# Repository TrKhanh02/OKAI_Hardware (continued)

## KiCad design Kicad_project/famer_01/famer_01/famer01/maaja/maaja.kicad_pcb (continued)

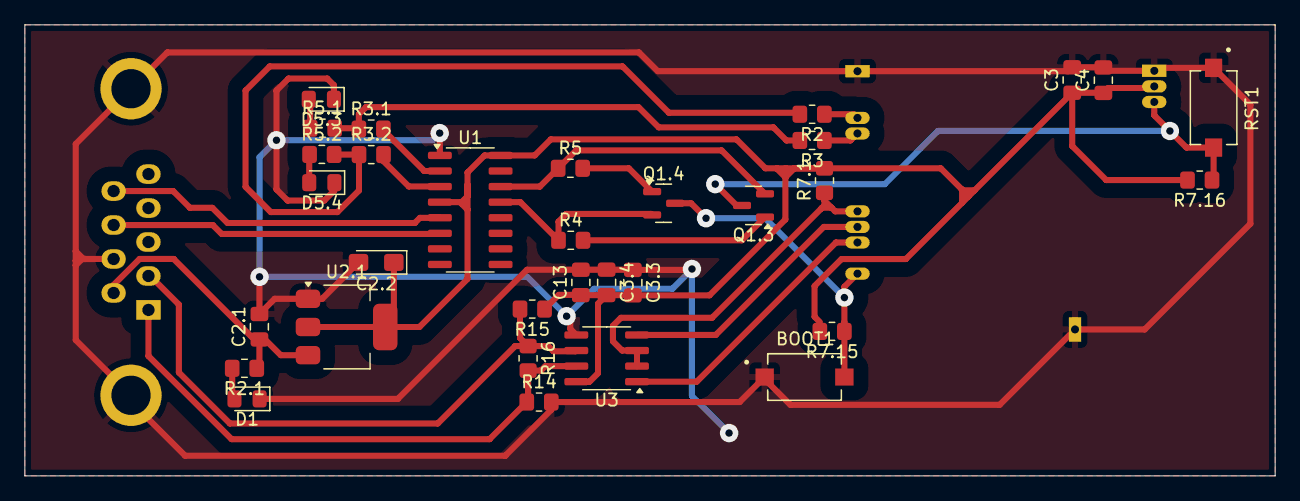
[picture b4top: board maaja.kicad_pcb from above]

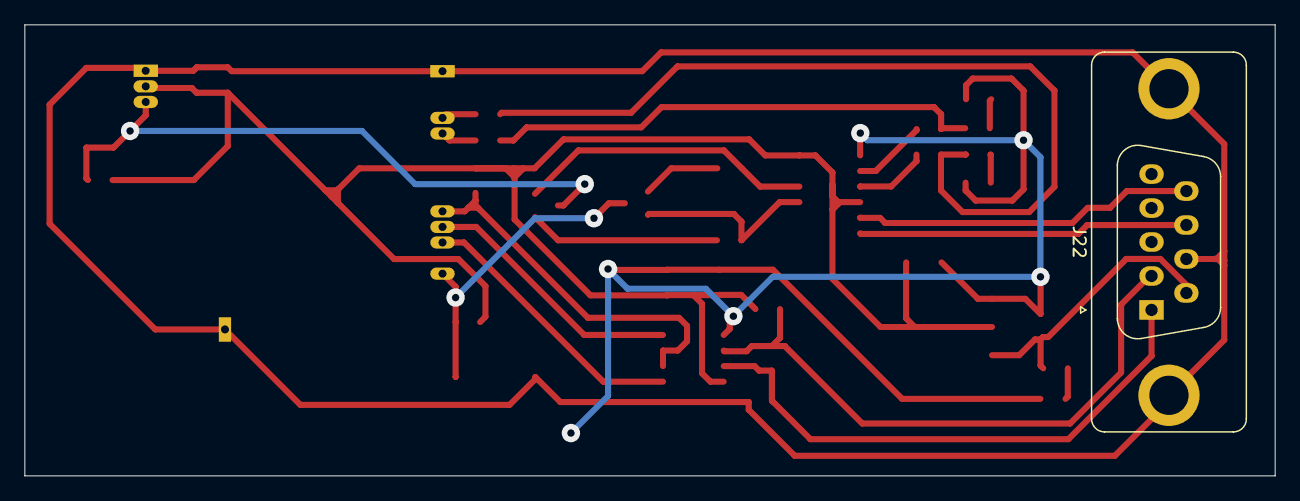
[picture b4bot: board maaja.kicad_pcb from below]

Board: 2 copper layers, 102.0 x 36.8 mm, 34 parts (2 on the bottom side), 25 nets.

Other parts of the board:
C3: 10uF; C_0805_2012Metric_Pad1.18x1.45mm_HandSolder
C4: 0.1uF; C_0805_2012Metric_Pad1.18x1.45mm_HandSolder
J2: ESP32; J header esp32
R7.1: 10k; R_0805_2012Metric_Pad1.20x1.40mm_HandSolder

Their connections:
/3.3V: C3.1, C4.1, J2.2, R7.1.2; also elsewhere on the board
/EN: J2.3; also elsewhere on the board
/IO0: J2.25; also elsewhere on the board
/IO5: J2.29, R7.1.1; also elsewhere on the board
/IO16: J2.27; also elsewhere on the board
/IO17: J2.28; also elsewhere on the board
/MCU_RXD0: J2.34; also elsewhere on the board
/MCU_TXD0: J2.35; also elsewhere on the board
GND: C3.2, C4.2, J2.1, J2.15, J2.38; also elsewhere on the board

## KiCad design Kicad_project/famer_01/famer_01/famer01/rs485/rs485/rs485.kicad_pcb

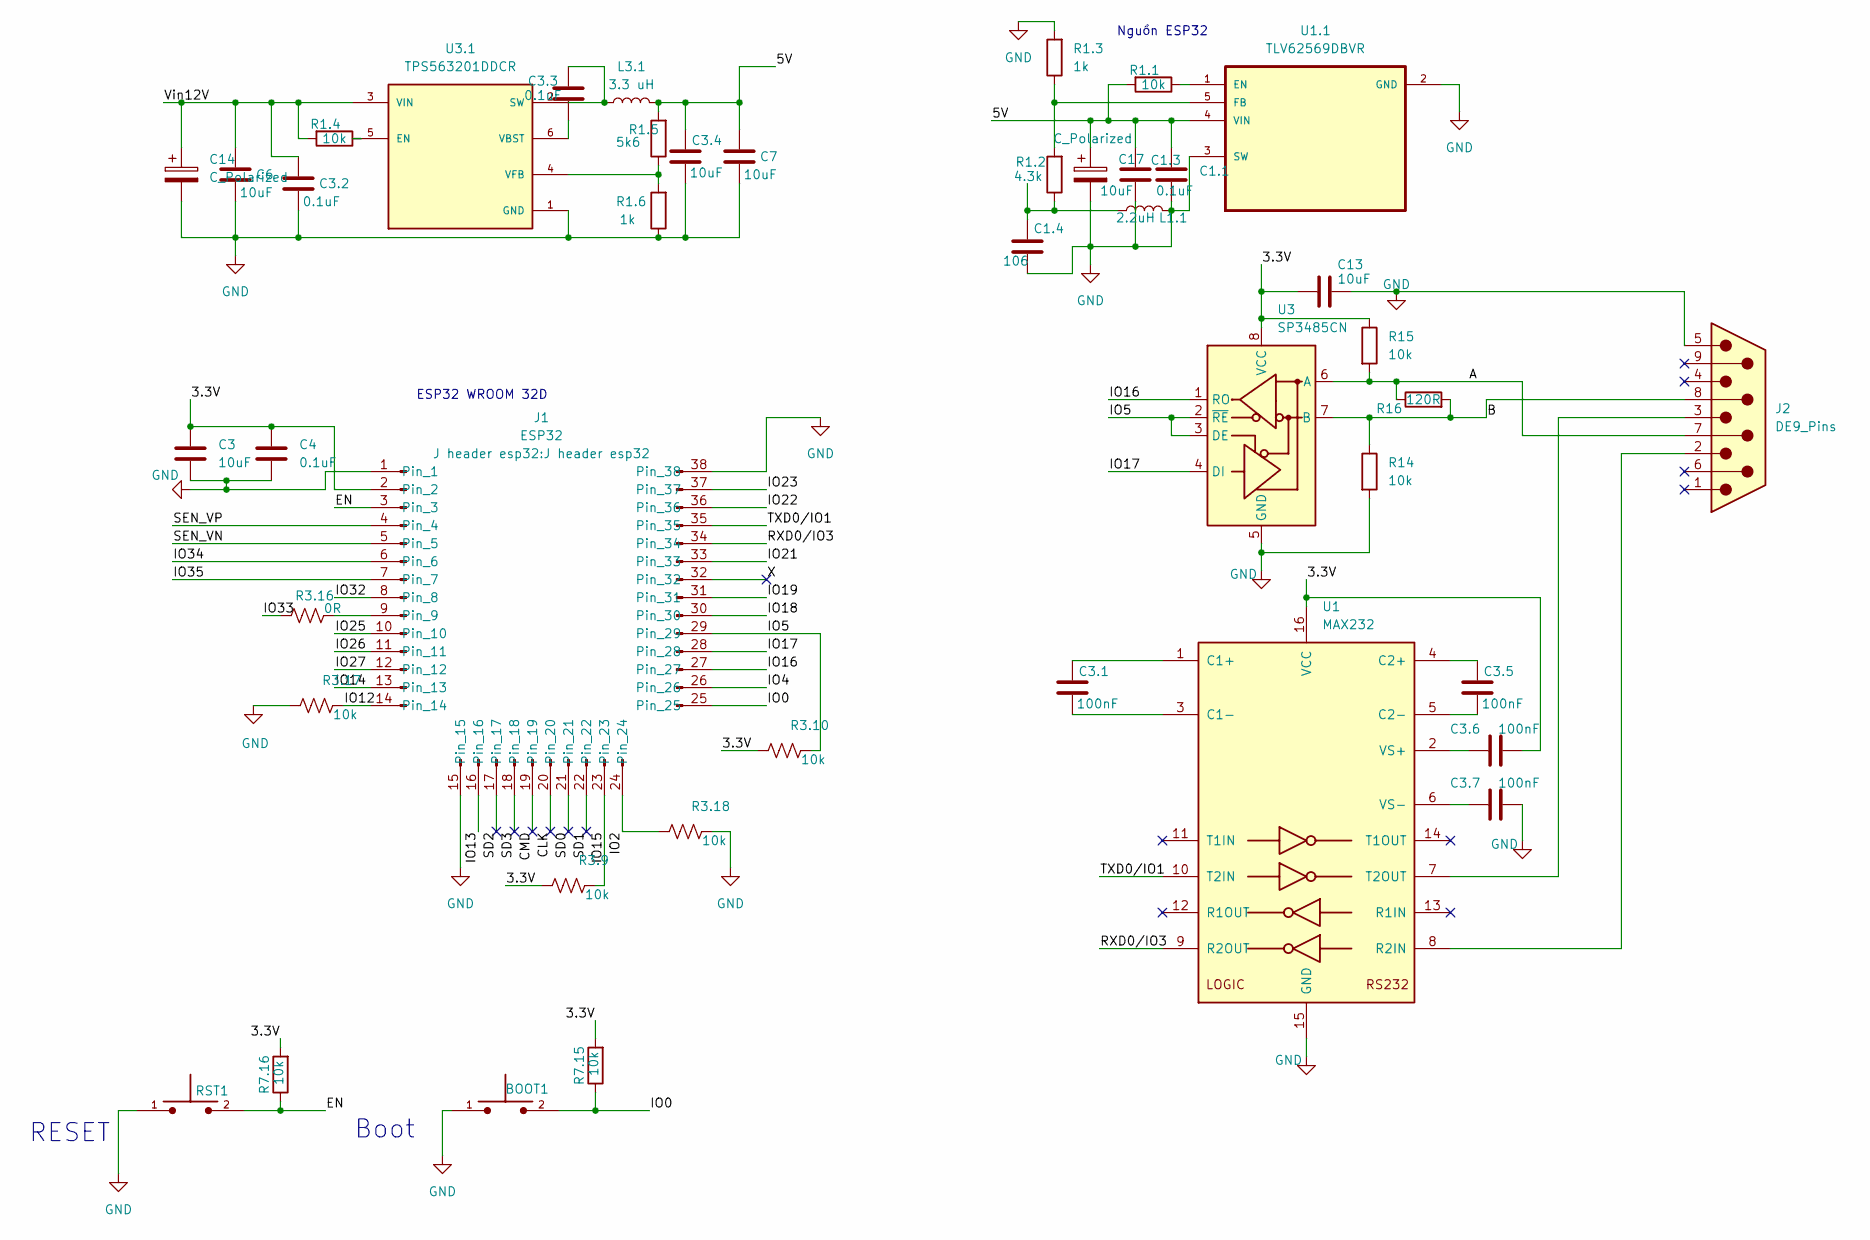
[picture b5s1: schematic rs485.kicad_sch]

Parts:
BOOT1: TS10-63-26-BE-250-SMT-TR; SW_TS10-63-26-BE-250-SMT-TR; PARTREV 1.0
C1.1, C3.2, C3.3, C4: 0.1uF; C_0805_2012Metric_Pad1.18x1.45mm_HandSolder
C1.3, C3, C3.4, C6, C7, C13: 10uF; C_0805_2012Metric_Pad1.18x1.45mm_HandSolder
C1.4: 106; C_0805_2012Metric_Pad1.18x1.45mm_HandSolder
C3.1, C3.5, C3.6, C3.7: 100nF; C_0805_2012Metric_Pad1.18x1.45mm_HandSolder
C14, C17: C_Polarized; CP_Elec_6.3x7.7
J1: ESP32; J header esp32
J2: DE9_Pins; DSUB-9_Pins_Vertical_P2.77x2.84mm
L1.1: 2.2uH; IND_SLF7032T-331MR22-2PF
L3.1: 3.3 uH; IND_SLF7032T-331MR22-2PF
R1.1, R1.4, R3.9, R3.10, R3.17, R3.18, R7.15, R7.16, R14, R15: 10k; R_0805_2012Metric_Pad1.20x1.40mm_HandSolder
R1.2: 4.3k; R_0805_2012Metric_Pad1.20x1.40mm_HandSolder
R1.3, R1.6: 1k; R_0805_2012Metric_Pad1.20x1.40mm_HandSolder
R1.5: 5k6; R_0805_2012Metric_Pad1.20x1.40mm_HandSolder
R3.16: 0R; R_0805_2012Metric_Pad1.20x1.40mm_HandSolder
R16: 120R; R_0805_2012Metric_Pad1.20x1.40mm_HandSolder
RST1: TS10-63-26-BE-250-SMT-TR; SW_TS10-63-26-BE-250-SMT-TR; PARTREV 1.0
U1: MAX232; DIP-16_W7.62mm_SMDSocket_SmallPads
U1.1: TLV62569DBVR; SOT95P280X145-5N
U3: SP3485CN; SOIC-8_3.9x4.9mm_P1.27mm
U3.1: TPS563201DDCR; SOT95P280X110-6N; PARTREV December 2015

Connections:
/3.3V: C3.1, C3.6.2, C4.1, C13.1, J1.2, R3.9.1, R3.10.1, R7.15.2, R7.16.2, R15.1, U1.16 (VCC), U3.8 (VCC)
/5V: C1.1.1, C1.3.1, C3.4.1, C7.1, C17.1, L3.1.2, R1.1.2, R1.5.2, U1.1.4 (VIN)
/ A: J2.7, R15.2, R16.1, U3.6 (A)
/ B: J2.8, R14.1, R16.2, U3.7 (B)
/CLK: J1.20
/CLK_1: J1.20
/CMD: J1.19
/CMD_1: J1.19
/EN: J1.3, R7.16.1, RST1.2
/IO0: BOOT1.2, J1.25, R7.15.1
/IO2: J1.24, R3.18.1
/IO4: J1.26
/IO5: J1.29, R3.10.2, U3.2 (~RE), U3.3 (DE)
/IO12: J1.14, R3.17.2
/IO13: J1.16
/IO14: J1.13
/IO15: J1.23, R3.9.2
/IO16: J1.27, U3.1 (RO)
/IO17: J1.28, U3.4 (DI)
/IO18: J1.30
/IO19: J1.31
/IO21: J1.33
/IO22: J1.36
/IO23: J1.37
/IO25: J1.10
/IO26: J1.11
/IO27: J1.12
/IO32: J1.8
/IO33: R3.16.1
/IO34: J1.6
/IO35: J1.7
/RXD0/IO3: J1.34, U1.9 (R2OUT)
/SD0: J1.21
/SD0_1: J1.21
/SD1: J1.22
/SD1_1: J1.22
/SD2: J1.17
/SD2_1: J1.17
/SD3: J1.18
/SD3_1: J1.18
/SEN_VN: J1.5
/SEN_VP: J1.4
/TXD0/IO1: J1.35, U1.10 (T2IN)
/Vin12V: C3.2.1, C6.1, C14.1, R1.4.2, U3.1.3 (VIN)
/X: J1.32
/X_1: J1.32
GND: BOOT1.1, C1.1.2, C1.3.2, C1.4.2, C3.2, C3.2.2, C3.4.2, C3.7.2, C4.2, C6.2, C7.2, C13.2, C14.2, C17.2, J1.1, J1.15, J1.38, J2.5, L1.1.2, R1.3.2, R1.6.1, R3.17.1, R3.18.2, R14.2, RST1.1, U1.15 (GND), U1.1.2 (GND), U1.1.3 (SW), U3.5 (GND), U3.1.1 (GND)
unnamed: C1.4.1, L1.1.1, R1.2.1
unnamed: J1.9, R3.16.2
unnamed: C3.1.1, U1.1 (C1+)
unnamed: C3.1.2, U1.3 (C1-)
unnamed: C3.5.1, U1.4 (C2+)
unnamed: C3.5.2, U1.5 (C2-)
unnamed: J2.2, U1.8 (R2IN)
unnamed: J2.3, U1.7 (T2OUT)
unnamed: C3.6.1, U1.2 (VS+)
unnamed: C3.7.1, U1.6 (VS-)
unnamed: R1.1.1, U1.1.1 (EN)
unnamed: R1.2.2, R1.3.1, U1.1.5 (FB)
unnamed: R1.4.1, U3.1.5 (EN)
unnamed: C3.3.1, L3.1.1, U3.1.2 (SW)
unnamed: C3.3.2, U3.1.6 (VBST)
unnamed: R1.5.1, R1.6.2, U3.1.4 (VFB)

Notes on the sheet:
ESP32 WROOM 32D
Nguồn ESP32
Boot
RESET

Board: 2 copper layers, 43 parts (0 on the bottom side), 32 nets, no tracks yet.

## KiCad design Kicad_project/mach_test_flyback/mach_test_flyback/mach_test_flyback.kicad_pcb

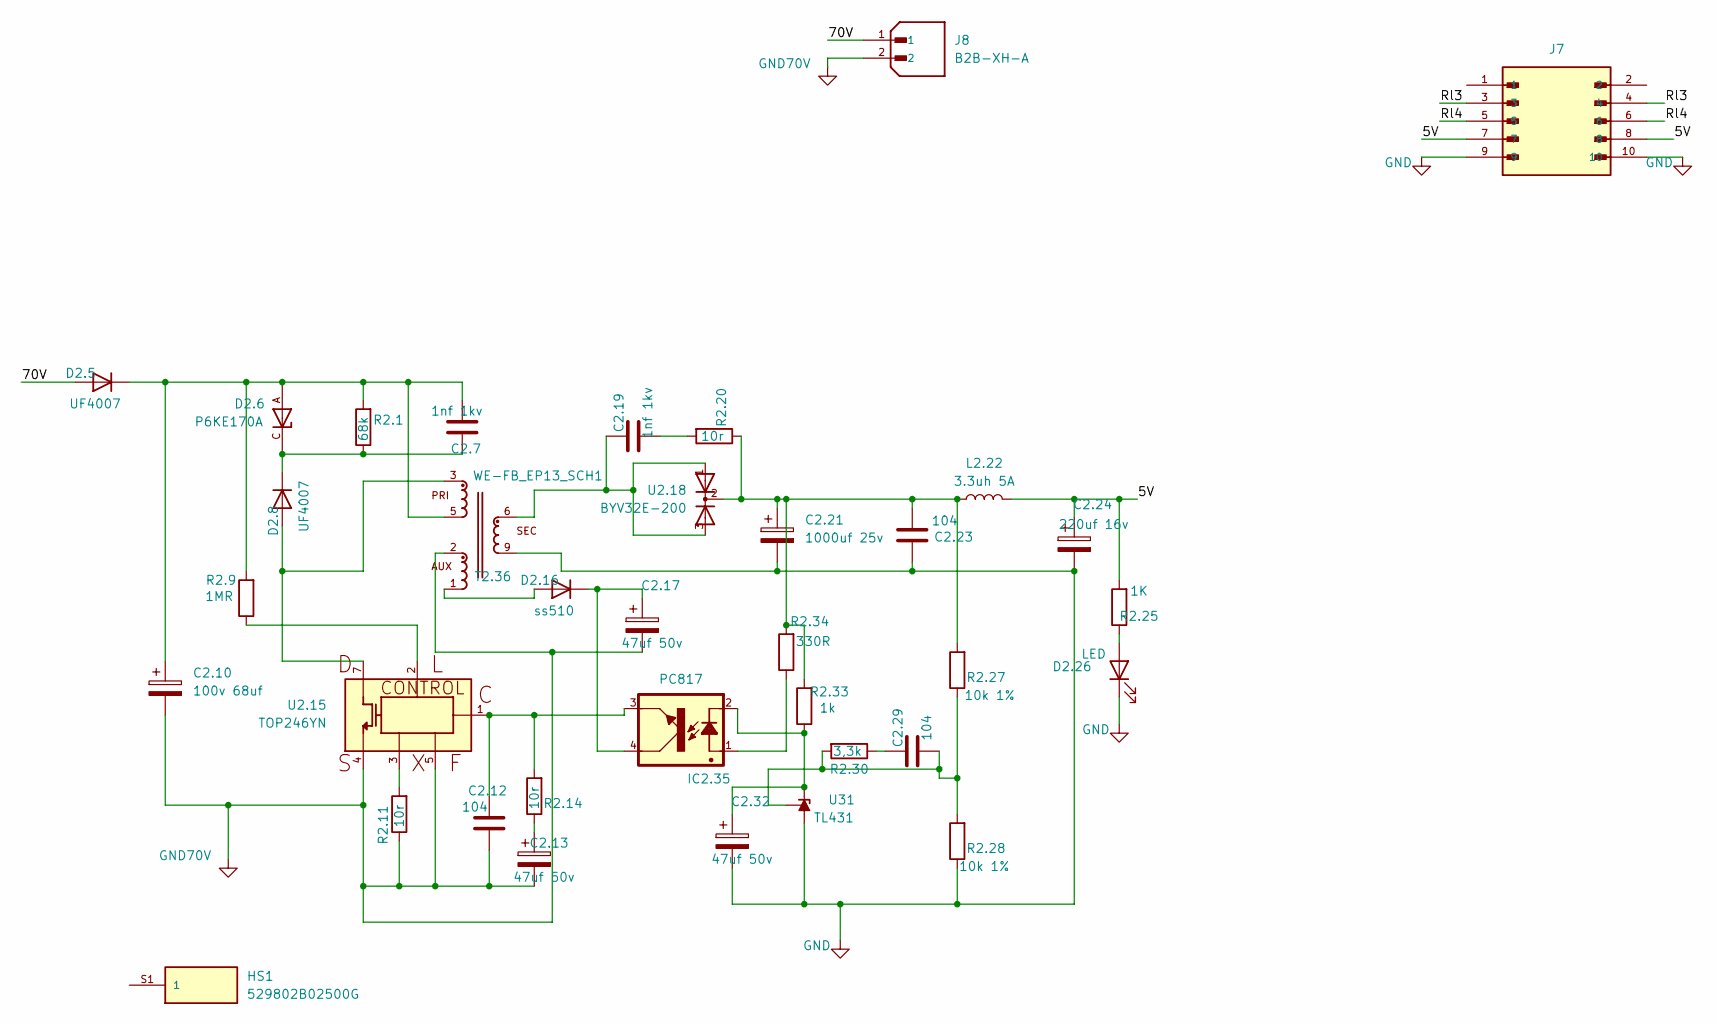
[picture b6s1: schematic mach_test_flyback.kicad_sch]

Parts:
C2.7, C2.19: 1nf 1kv; C_Axial_L3.8mm_D2.6mm_P7.50mm_Horizontal
C2.10: 100v 68uf; CP_Radial_D8.0mm_P3.80mm
C2.12, C2.23, C2.29: 104; C_0805_2012Metric
C2.13, C2.17, C2.32: 47uf 50v; CP_Elec_6.3x5.4
C2.21: 1000uf 25v; CP_Radial_D8.0mm_P3.80mm
C2.24: 220uf 16v; CP_Elec_6.3x5.4
D2.5, D2.8: UF4007; D_MELF
D2.6: P6KE170A; DIOAD1300W80L670D310; PARTREV K2105
D2.16: ss510; D_MELF
D2.26: LED; LED_0805_2012Metric
HS1: 529802B02500G; HSINK_529802B02500G; PARTREV 1.0
IC2.35: PC817; LED_OPSCO_SK6812_PLCC4_5.0x5.0mm_P3.1mm; DIGIKEY 160-1367-5-ND
J7: N2510-5002-RB; 3M_N2510-5002-RB; PARTREV S
J8: B2B-XH-A; JST_B2B-XH-A; PARTREV N/A
L2.22: 3.3uh 5A; L_10.4x10.4_H4.8
R2.1: 68k; R_2512_6332Metric_Pad1.40x3.35mm_HandSolder
R2.9: 1MR; R_1210_3225Metric_Pad1.30x2.65mm_HandSolder
R2.11, R2.14, R2.20: 10r; R_0805_2012Metric
R2.25: 1K; R_0805_2012Metric
R2.27, R2.28: 10k 1%; R_0805_2012Metric
R2.30: 3,3k; R_0805_2012Metric
R2.33: 1k; R_0805_2012Metric
R2.34: 330R; R_0805_2012Metric
T2.36: WE-FB_EP13_SCH1; WE-FB_EP13_P16.36
U2.15: TOP246YN; IC_TOP246YN; PARTREV 0
U2.18: BYV32E-200; TO220
U31: TL431; SOT-23

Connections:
/5V: C2.24.1, J7.7, J7.8, L2.22.2, R2.25.2
/70V: D2.5.2 (A), J8.1
/Rl3: J7.3, J7.4
/Rl4: J7.5, J7.6
GND: C2.21.2, C2.23.2, C2.24.2, C2.32.2, D2.26.1 (K), J7.9, J7.10, R2.28.1, T2.36.9, T2.36.10, U31.3 (A)
GND70V: C2.10.2, C2.12.2, C2.13.2, C2.17.2, J8.2, R2.11.1, T2.36.2, U2.15.4, U2.15.5
unnamed: C2.12.1, IC2.35.3, R2.14.2, U2.15.1
unnamed: C2.13.1, R2.14.1
unnamed: C2.19.1, R2.20.2
unnamed: C2.19.2, T2.36.6, T2.36.7, U2.18.1, U2.18.3
unnamed: C2.21.1, C2.23.1, L2.22.1, R2.20.1, R2.27.2, R2.33.2, R2.34.2, U2.18.2
unnamed: C2.29.2, R2.30.1
unnamed: C2.7.1, C2.10.1, D2.5.1 (K), D2.6.A, R2.1.2, R2.9.2, T2.36.5
unnamed: D2.8.2 (A), T2.36.3, U2.15.7
unnamed: C2.7.2, D2.6.C, D2.8.1 (K), R2.1.1
unnamed: D2.16.2 (A), T2.36.1
unnamed: C2.17.1, D2.16.1 (K), IC2.35.4
unnamed: D2.26.2 (A), R2.25.1
unnamed: HS1.S1 (1), HS1.S2 (1)
unnamed: IC2.35.1, R2.34.1
unnamed: R2.9.1, U2.15.2
unnamed: R2.11.2, U2.15.3
unnamed: C2.32.1, IC2.35.2, R2.33.1, U31.2 (K)
unnamed: C2.29.1, R2.27.1, R2.28.2, R2.30.2, U31.1 (REF)

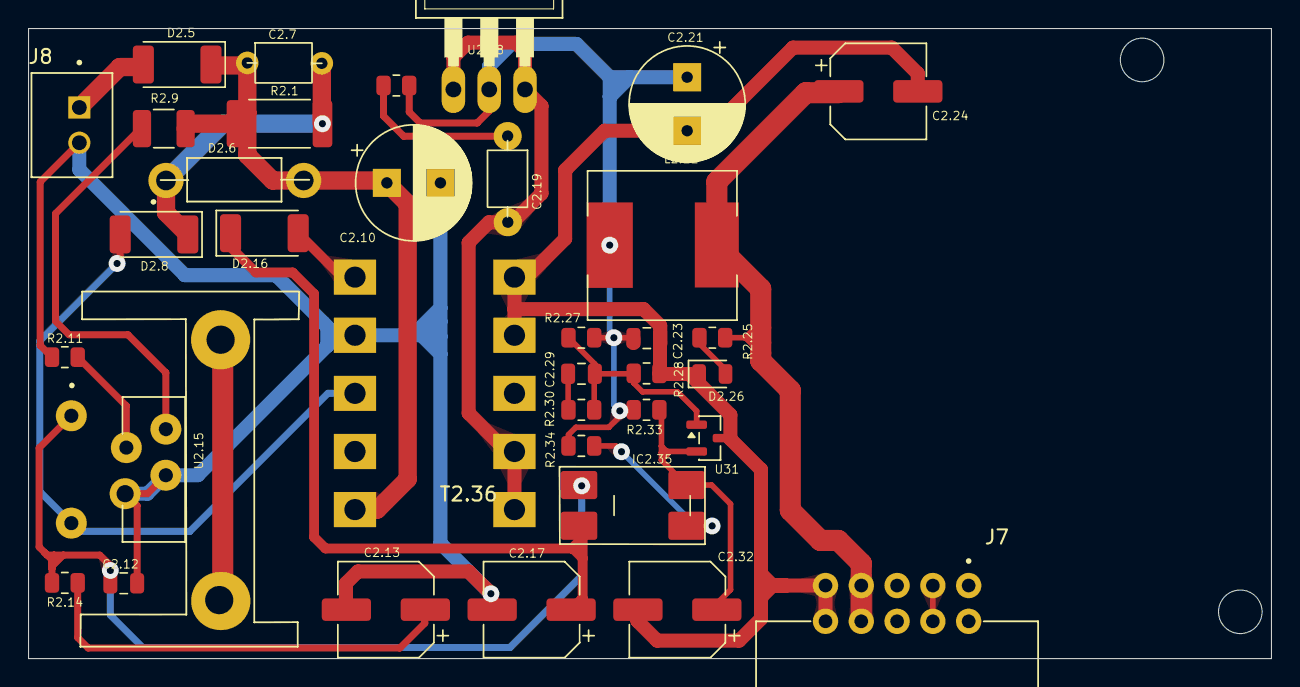
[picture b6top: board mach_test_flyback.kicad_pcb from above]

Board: 2 copper layers, 88.2 x 44.7 mm, 36 parts (1 on the bottom side), 24 nets.

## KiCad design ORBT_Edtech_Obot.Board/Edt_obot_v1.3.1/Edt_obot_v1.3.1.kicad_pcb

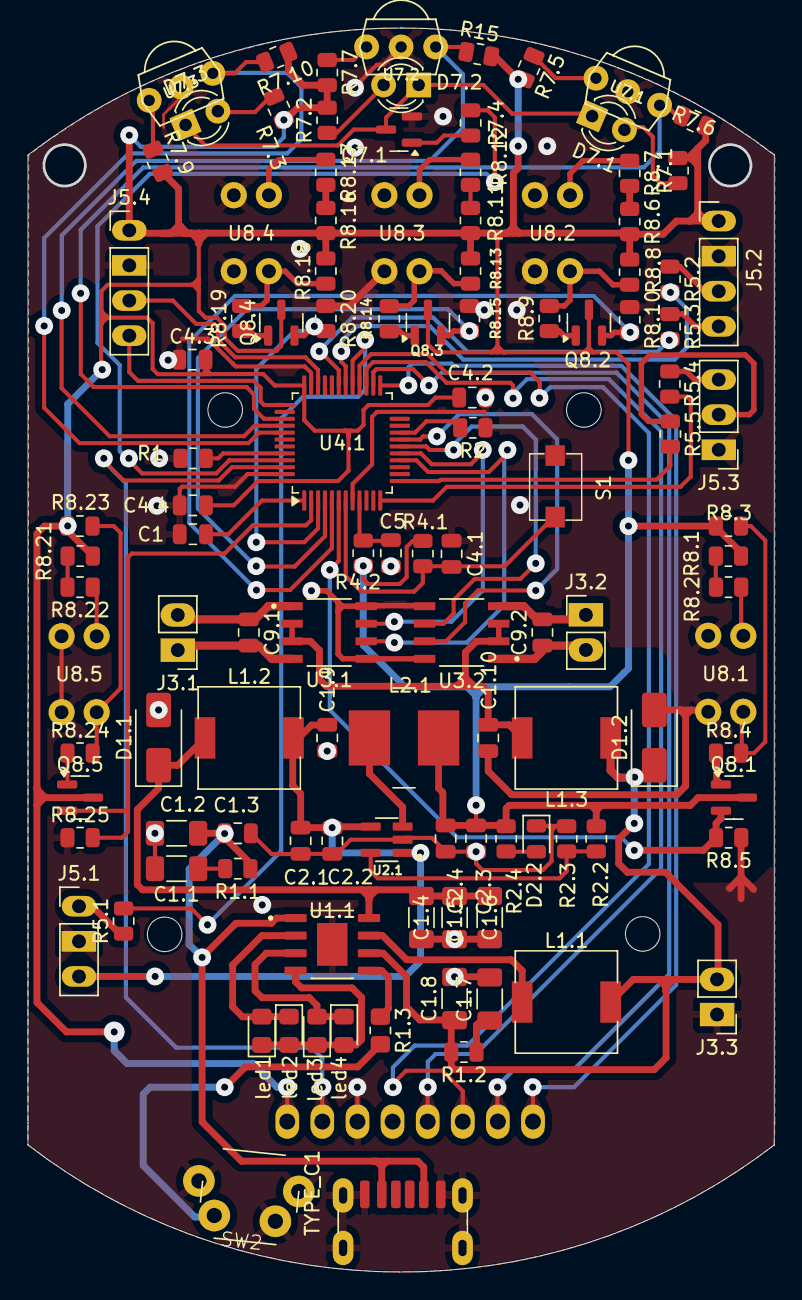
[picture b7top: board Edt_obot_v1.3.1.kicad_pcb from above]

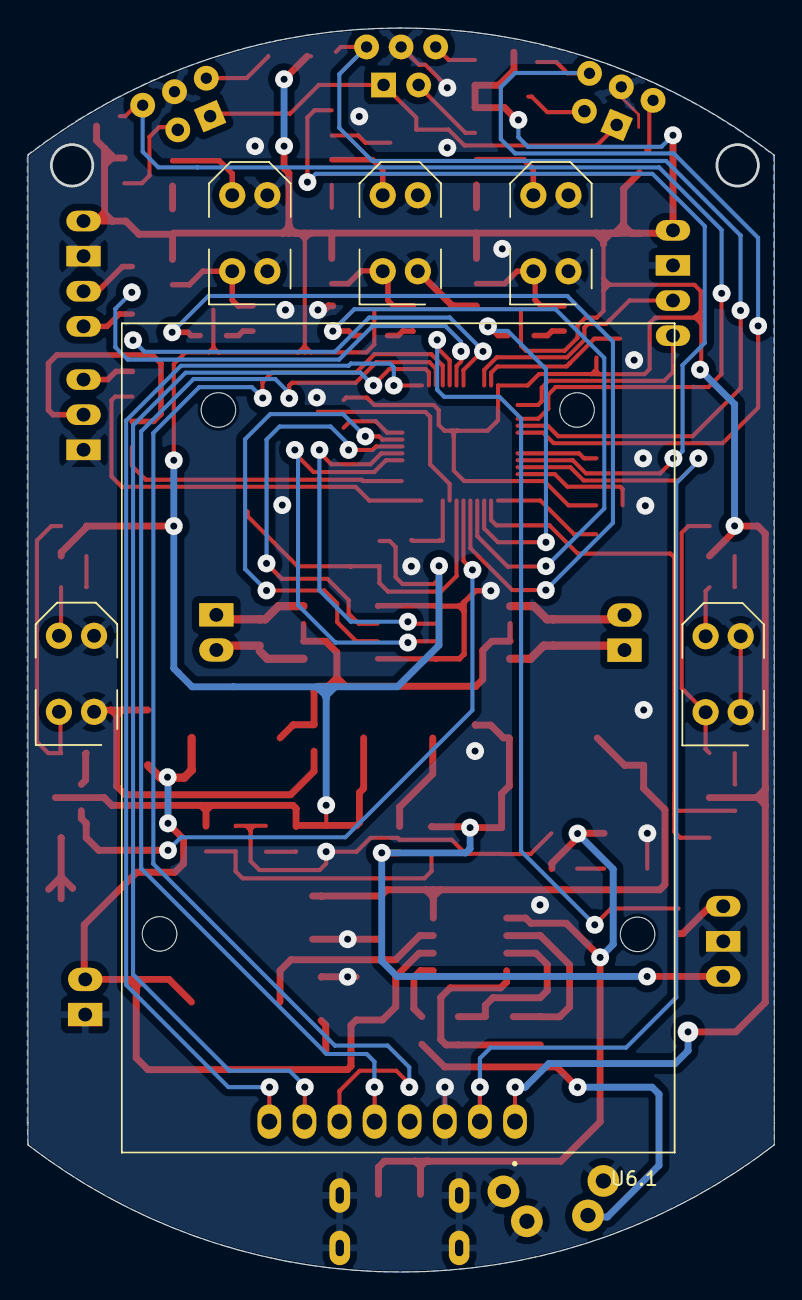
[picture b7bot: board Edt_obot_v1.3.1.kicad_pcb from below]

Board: 2 copper layers, 54.0 x 90.0 mm, 116 parts (6 on the bottom side), 85 nets.

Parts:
C1, C1.3, C4.1, C4.2, C4.3, C4.4, C5, C9.1, C9.2: 104; C_0805_2012Metric
C1.1, C1.2: 106; C_1206_3216Metric_Pad1.33x1.80mm_HandSolder
C1.4, C1.5, C1.6: 22 UF; C_1206_3216Metric_Pad1.33x1.80mm_HandSolder
C1.7: 22uf; C_1206_3216Metric_Pad1.33x1.80mm_HandSolder
C1.8: 22uF; C_1206_3216Metric_Pad1.33x1.80mm_HandSolder
C1.9, C1.10, C2.1, C2.4: 10uF; C_0805_2012Metric
C2.2, C2.3: 0.1uF; C_0805_2012Metric
D1.1, D1.2: SS34; D_SMA
D2.2: LED; LED_0805_2012Metric
D7.1, D7.2, D7.3: IR7393C; LED_D3.0mm_IRBlack
J3.1: MT1; PinHeader_1x02_P2.54mm_Vertical
J3.2, J3.3: MT2; PinHeader_1x02_P2.54mm_Vertical
J5.1: LED; PinHeader_1x03_P2.54mm_Vertical
J5.2: UART_Debug; PinHeader_1x04_P2.54mm_Vertical
J5.3: UART_ESP; PinHeader_1x03_P2.54mm_Vertical
J5.4: Bootloader; PinHeader_1x04_P2.54mm_Vertical
L1.1: 1R; L_7.3x7.3_H4.5
L1.2, L1.3: L; L_7.3x7.3_H4.5
L2.1: 22uH; L_Ferrocore_DLG-0705
Q7.1, Q8.1, Q8.2, Q8.3, Q8.4, Q8.5: SS8050; SOT-23
R1, R2, R2.2, R4.1, R7.1, R7.2, R7.3, R7.6, R7.10, R8.3, R8.5, R8.8, R8.10, R8.13, R8.15, R8.18, R8.20, R8.23, R8.25: 10K; R_0805_2012Metric
R1.1, R1.2: 2R; R_0805_2012Metric
R1.3: 10k; R_0805_2012Metric_Pad1.20x1.40mm_HandSolder
R2.3: 2.2K; R_0805_2012Metric
R2.4, R7.4, R8.4, R8.9, R8.14, R8.19, R8.24: 1K; R_0805_2012Metric
R4.2, R5.1, R5.2, R5.3, R5.4, R5.5: 0R; R_0805_2012Metric
R7.5, R7.7, R7.9: 100R; R_0805_2012Metric
R8.1, R8.2: 150R; R_0805_2012Metric
R8.6, R8.7, R8.11, R8.12, R8.16, R8.17, R8.21, R8.22: 680R; R_0805_2012Metric
R15: R7.8; R_0805_2012Metric
S1: RST; SW_TS10-63-26-BE-250-SMT-TR
SW2: SW
TYPE_C1: USB_C_Receptacle_PowerOnly_6P; USB_C_Receptacle_GCT_USB4125-xx-x_6P_TopMnt_Horizontal
U1.1: IP5306; SOP127P600X165-9N
U2.1: TLV62569PDDCR; SOT95P280X110-6N
U3.1, U3.2: L9110S; SOIC127P599X172-8N
U4.1: CH32V203CxTx; LQFP-48_7x7mm_P0.5mm
U6.1: RFID; MODULE_CEG006900
U7.1, U7.2, U7.3: TSOP1838; TSOP18XX
U8.1, U8.2, U8.3, U8.4, U8.5: TCRT5000; OPTO_TCRT5000
led1: <25; LED_0805_2012Metric_Pad1.15x1.40mm_HandSolder
led2: <50; LED_0805_2012Metric_Pad1.15x1.40mm_HandSolder
led3: <75; LED_0805_2012Metric_Pad1.15x1.40mm_HandSolder
led4: >75; LED_0805_2012Metric_Pad1.15x1.40mm_HandSolder

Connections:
+3.3V: C2.3.1, C2.4.1, C4.2.2, C4.3.2, C4.4.2, J5.2.1, J5.4.1, L2.1.1, Q8.1.3 (C), Q8.2.3 (C), Q8.3.3 (C), Q8.4.3 (C), Q8.5.3 (C), R2.2.2, R2.4.2, R4.1.1, R4.2.2, R7.1.2, R7.2.2, R7.3.2, R7.5.2, R7.6.1, R7.7.2, R7.9.2, R7.10.1, R8.1.2, R8.3.2, R8.6.2, R8.8.2, R8.11.2, R8.13.2, R8.16.2, R8.18.2, R8.21.2, R8.23.2, R15.1, U4.1.24 (VDD_VIO_1), U4.1.36 (VDD_2), U4.1.48 (VDD_VIO_3), U6.1.1 (VCC)
/2: U1.1.2 (LED1), led1.2 (A), led2.1 (K)
/3: U1.1.3 (LED2), led3.2 (A), led4.1 (K)
/3V7_BAT: C1.8.1, D1.2.1 (K), J3.3.2, L1.1.2, L1.3.1, R1.2.2, U1.1.6 (BAT)
/4: U1.1.4 (LED3), led1.1 (K), led2.2 (A), led3.1 (K), led4.2 (A)
/5V: C1.9.2, C2.1.1, C2.2.1, J5.1.3, L1.2.2, U2.1.1 (EN), U2.1.4 (VIN)
/5V_BAT: C1.4.2, C1.5.2, C1.6.2, D1.1.1 (K), L1.2.1, U1.1.8 (VOUT)
/5V_USB: C1.2.1, C1.3.1, R1.1.2, TYPE_C1.A9 (VBUS), TYPE_C1.B9 (VBUS), U1.1.1 (VIN)
/BOOT0: R1.2, U4.1.44 (BOOT0)
/BOOT1: R2.2, U4.1.20 (PB2/BOOT1)
/CS/SDA: U4.1.25 (PB12), U6.1.8 (SS/SDA/RX)
/FB_U1.1: R2.2.1, R2.3.2, U2.1.6 (FB)
/IA1: U3.1.6 (IA), U4.1.16 (PA6)
/IA2: U3.2.6 (IA), U4.1.18 (PB0)
/IB1: U3.1.7 (IB), U4.1.17 (PA7)
/IB2: U3.2.7 (IB), U4.1.19 (PB1)
/IR1: R7.6.2, U4.1.39 (PB3), U7.1.OUT
/IR2: R15.2, U4.1.40 (PB4), U7.2.OUT
/IR3: R7.10.2, U4.1.41 (PB5), U7.3.OUT
/LINE1: Q8.1.2 (E), R8.5.2, U4.1.6 (OSC_OUT/PD1)
/LINE2: Q8.2.2 (E), R8.10.2, U4.1.5 (OSC_IN/PD0)
/LINE3: Q8.3.2 (E), R8.15.2, U4.1.4 (PC15-OSC32_OUT)
/LINE4: Q8.4.2 (E), R8.20.2, U4.1.3 (PC14-OSC32_IN)
/LINE5: Q8.5.2 (E), R8.25.2, U4.1.2 (PC13-TAMPER-RTC)
/MISO: U4.1.27 (PB14), U6.1.5 (MISO/SCL/TX)
/MOSI: U4.1.28 (PB15), U6.1.6 (MOSI)
/OA1: C9.1.1, J3.1.2, U3.1.1 (OA)
/OA2: C9.2.1, J3.2.2, U3.2.1 (OA)
/OB1: C9.1.2, J3.1.1, U3.1.4 (OB)
/OB2: C9.2.2, J3.2.1, U3.2.4 (OB)
/PA2: R5.4.2, U4.1.12 (PA2)
/PA3: R5.5.2, U4.1.13 (PA3)
/PA8: R5.1.2, U4.1.29 (PA8)
/PA9: R5.2.2, U4.1.30 (PA9)
/PA10: R5.3.2, U4.1.31 (PA10)
/PA13: J5.4.3, U4.1.34 (PA13/SWDIO)
/PA14: J5.4.4, U4.1.37 (PA14/SWCLK)
/PB8: R7.4.2, U4.1.45 (PB8)
/PB9: U4.1.46 (PB9), U6.1.2 (RST)
/PB13: U4.1.26 (PB13), U6.1.7 (SCK)
/RX_Debug: J5.2.4, R5.3.1
/RX_ESP: J5.3.2, R5.5.1
/SENSE: C1.7.1, R1.2.1
/TX_Debug: J5.2.3, R5.2.1
/TX_ESP: J5.3.3, R5.4.1
/VDDA: C5.2, R4.2.1, U4.1.9 (VDDA)
/WS2812: J5.1.1, R5.1.1
GND: C1.2, C1.1.2, C1.2.2, C1.3.2, C1.4.1, C1.5.1, C1.6.1, C1.7.2, C1.8.2, C1.9.1, C1.10.1, C2.1.2, C2.2.2, C2.3.2, C2.4.2, C4.1.2, C4.2.1, C4.3.1, C4.4.1, C5.1, D1.1.2 (A), D1.2.2 (A), D2.2.1 (K), J3.3.1, J5.1.2, J5.2.2, J5.3.1, J5.4.2, Q7.1.2 (E), R1.1, R2.1, R2.3.1, R8.5.1, R8.10.1, R8.15.1, R8.20.1, R8.25.1, S1.1, SW2.2 (B), SW2.3 (H), SW2.4 (H), TYPE_C1.A12 (GND), TYPE_C1.B12 (GND), TYPE_C1.S1 (SHIELD), U1.1.9 (POWERPAD), U2.1.2 (GND), U3.1.5 (GND), U3.1.8 (GND), U3.2.5 (GND), U3.2.8 (GND), U4.1.8 (VSSA), U4.1.23 (VSS), U4.1.35 (VSS), U4.1.47 (VSS), U6.1.3 (GND), U7.1.GND, U7.2.GND, U7.3.GND, U8.1.CATH, U8.1.E, U8.2.CATH, U8.2.E, U8.3.CATH, U8.3.E, U8.4.CATH, U8.4.E, U8.5.CATH, U8.5.E
unnamed: C1.1.1, R1.1.1
unnamed: D2.2.2 (A), R2.4.1
unnamed: D7.1.2 (A), R7.1.1
unnamed: D7.1.1 (K), D7.2.1 (K), D7.3.1 (K), Q7.1.3 (C)
unnamed: D7.2.2 (A), R7.2.1
unnamed: D7.3.2 (A), R7.3.1
unnamed: Q7.1.1 (B), R7.4.1
unnamed: Q8.1.1 (B), R8.4.1
unnamed: Q8.2.1 (B), R8.9.1
unnamed: Q8.3.1 (B), R8.14.1
unnamed: Q8.4.1 (B), R8.19.1
unnamed: Q8.5.1 (B), R8.24.1
unnamed: R8.1.1, R8.2.2
unnamed: R8.2.1, U8.1.A
unnamed: R8.3.1, R8.4.2, U8.1.COLL
unnamed: R8.6.1, R8.7.2
unnamed: R8.7.1, U8.2.A
unnamed: R8.8.1, R8.9.2, U8.2.COLL
unnamed: R8.11.1, R8.12.2
unnamed: R8.12.1, U8.3.A
unnamed: R8.13.1, R8.14.2, U8.3.COLL
unnamed: R8.16.1, R8.17.2
unnamed: R8.17.1, U8.4.A
unnamed: R8.18.1, R8.19.2, U8.4.COLL
unnamed: R8.21.1, R8.22.2
unnamed: R8.22.1, U8.5.A
unnamed: R8.23.1, R8.24.2, U8.5.COLL
unnamed: R1.3.2, SW2.1 (A)
unnamed: R1.3.1, U1.1.5 (KEY)
unnamed: L1.1.1, U1.1.7 (SW)
unnamed: L2.1.2, U2.1.3 (SW)
unnamed: C1.1, U4.1.1 (VBAT)
unnamed: C4.1.1, R4.1.2, S1.2, U4.1.7 (~RST)
unnamed: R7.5.1, U7.1.VCC (V+)
unnamed: R7.7.1, U7.2.VCC (V+)
unnamed: R7.9.1, U7.3.VCC (V+)
VCC: C1.10.2, L1.3.2, U3.1.2 (VCC), U3.1.3 (VCC), U3.2.2 (VCC), U3.2.3 (VCC)
